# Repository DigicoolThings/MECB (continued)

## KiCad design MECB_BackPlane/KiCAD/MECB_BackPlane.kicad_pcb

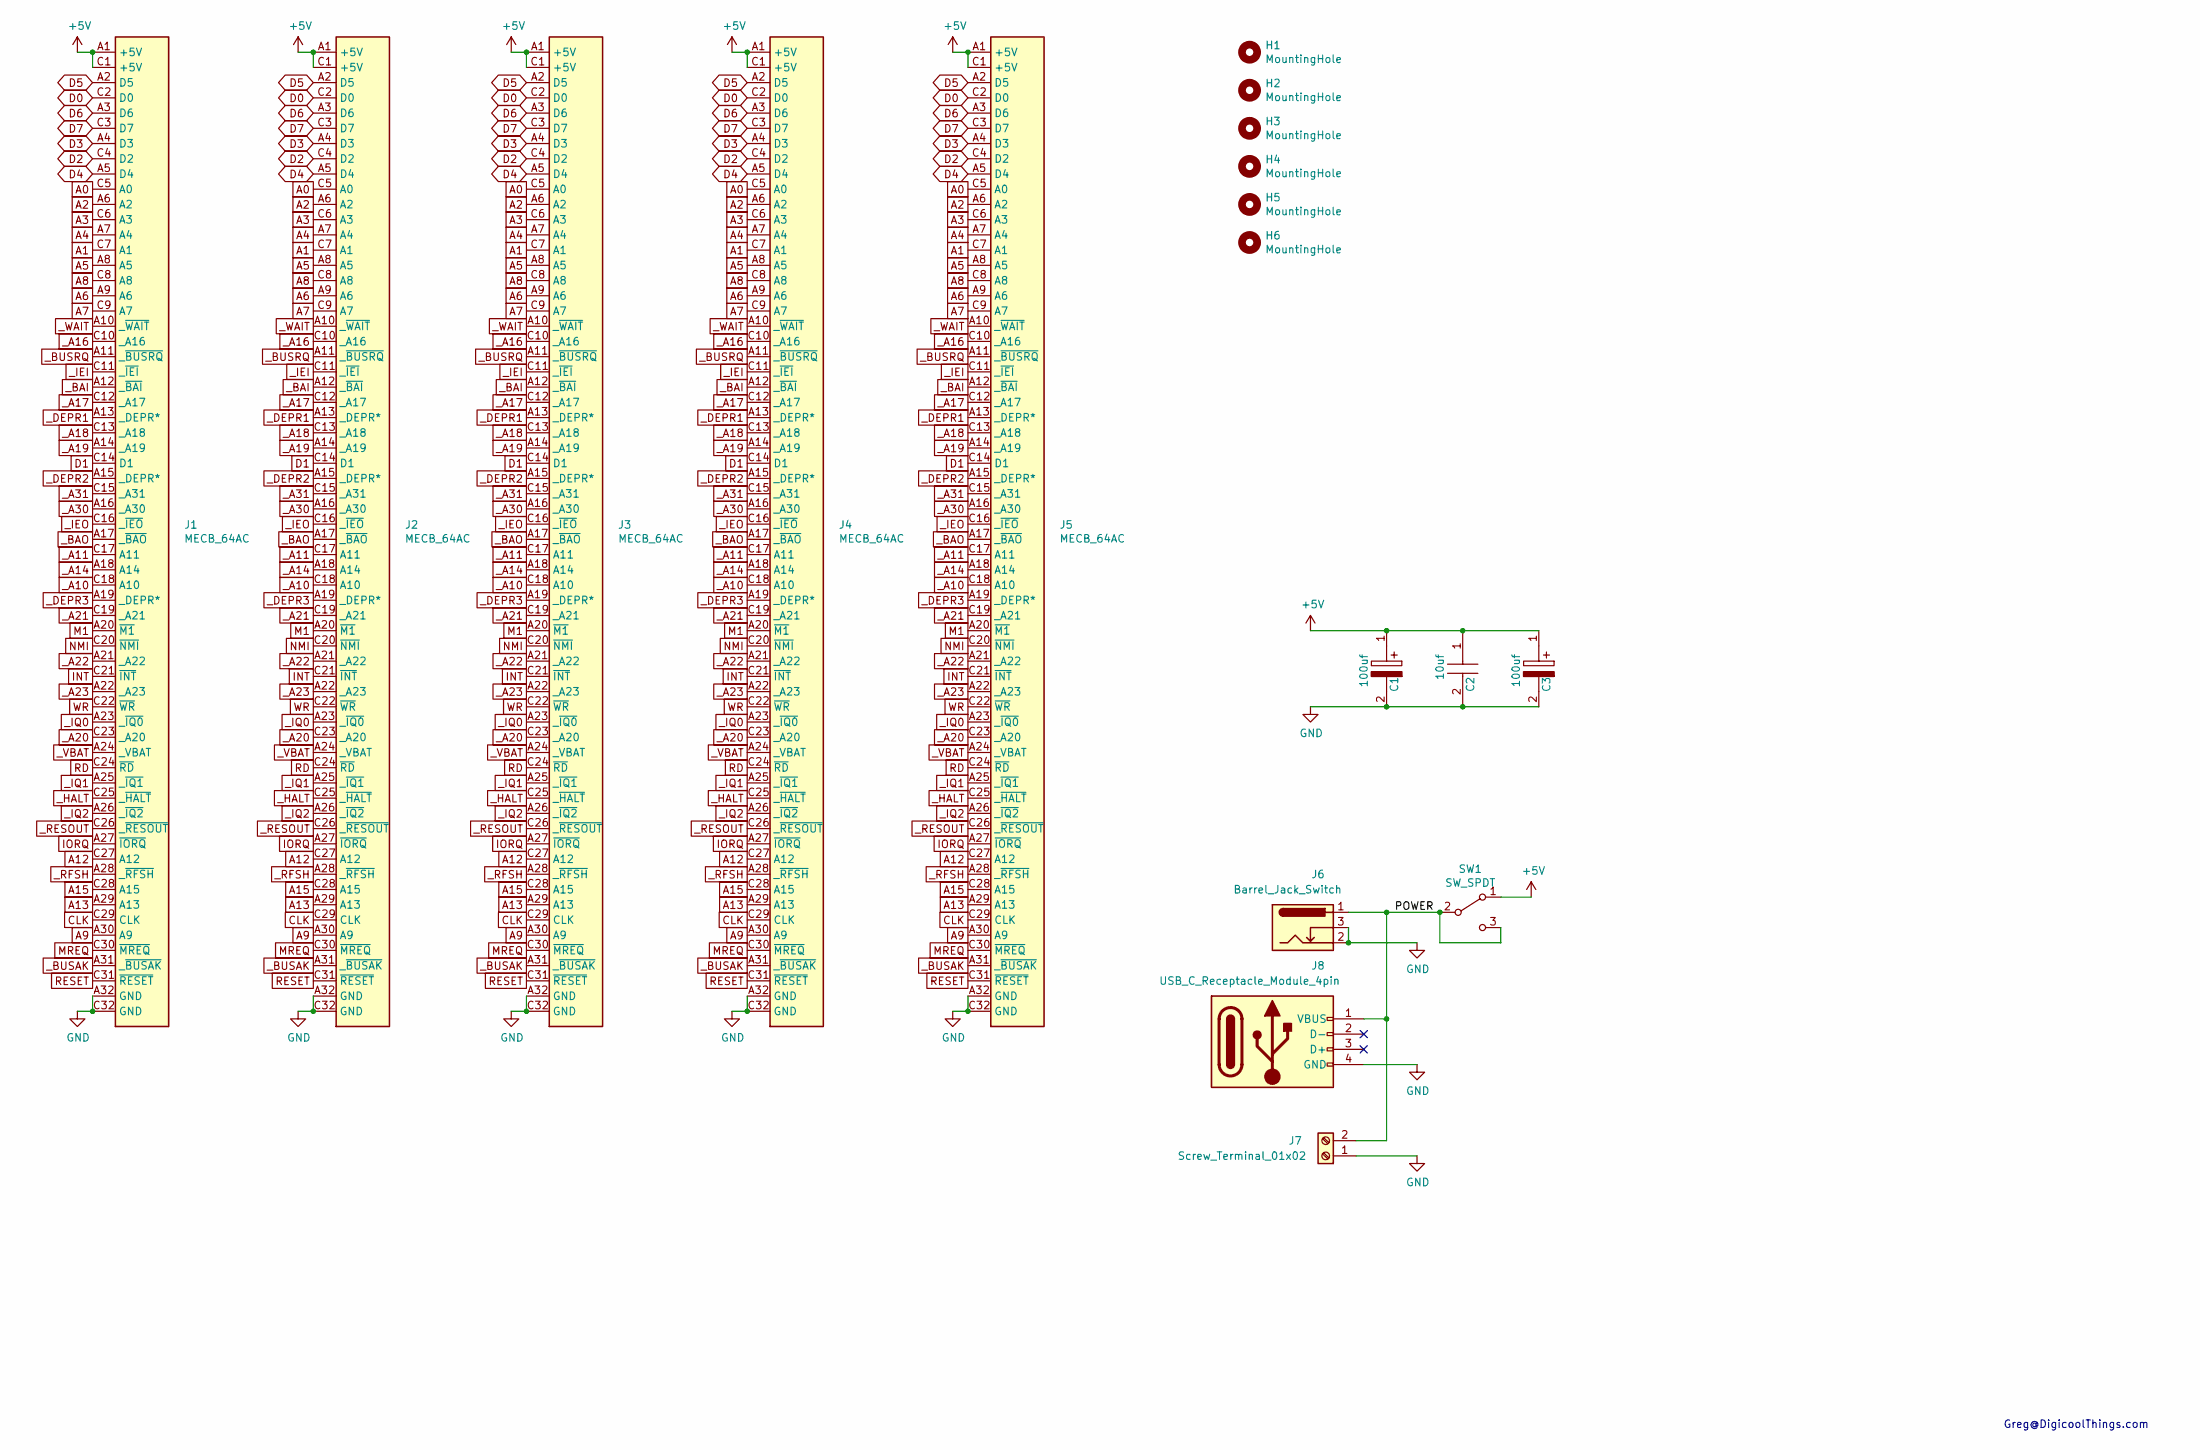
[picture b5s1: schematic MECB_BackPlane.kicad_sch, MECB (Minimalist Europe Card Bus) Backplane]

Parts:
C1, C3: 100uf; CAPPRD250W50D630H800-5mm
C2: 10uf; FG24
H1, H2, H3, H4, H5, H6: MountingHole; MountingHole_3.2mm_M3
J1, J2, J3, J4: MECB_64AC; DIN41612_C_2x32_C64AC_Female_Vertical_THT
J5: MECB_64AC; DIN41612_C_2x32_C64AC_Female_Horizontal_THT
J6: Barrel_Jack_Switch; BarrelJack_Horizontal
J7: Screw_Terminal_01x02; TerminalBlock_Philmore_TB132_1x02_P5.00mm_Horizontal
J8: USB_C_Receptacle_Module_4pin; USB_Module_4pin_Header_P2.54mm
SW1: SW_SPDT; Switch-SPST-4.7-lug

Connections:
+5V: C1.1, C2.1, C3.1, J1.A1 (+5V), J1.C1 (+5V), J2.A1 (+5V), J2.C1 (+5V), J3.A1 (+5V), J3.C1 (+5V), J4.A1 (+5V), J4.C1 (+5V), J5.A1 (+5V), J5.C1 (+5V), SW1.1 (A)
/POWER: J6.1, J7.2, J8.1 (VBUS), SW1.2 (B), SW1.3 (C)
A0: J1.C5 (A0), J2.C5 (A0), J3.C5 (A0), J4.C5 (A0), J5.C5 (A0)
A1: J1.C7 (A1), J2.C7 (A1), J3.C7 (A1), J4.C7 (A1), J5.C7 (A1)
A2: J1.A6 (A2), J2.A6 (A2), J3.A6 (A2), J4.A6 (A2), J5.A6 (A2)
A3: J1.C6 (A3), J2.C6 (A3), J3.C6 (A3), J4.C6 (A3), J5.C6 (A3)
A4: J1.A7 (A4), J2.A7 (A4), J3.A7 (A4), J4.A7 (A4), J5.A7 (A4)
A5: J1.A8 (A5), J2.A8 (A5), J3.A8 (A5), J4.A8 (A5), J5.A8 (A5)
A6: J1.A9 (A6), J2.A9 (A6), J3.A9 (A6), J4.A9 (A6), J5.A9 (A6)
A7: J1.C9 (A7), J2.C9 (A7), J3.C9 (A7), J4.C9 (A7), J5.C9 (A7)
A8: J1.C8 (A8), J2.C8 (A8), J3.C8 (A8), J4.C8 (A8), J5.C8 (A8)
A9: J1.A30 (A9), J2.A30 (A9), J3.A30 (A9), J4.A30 (A9), J5.A30 (A9)
A12: J1.C27 (A12), J2.C27 (A12), J3.C27 (A12), J4.C27 (A12), J5.C27 (A12)
A13: J1.A29 (A13), J2.A29 (A13), J3.A29 (A13), J4.A29 (A13), J5.A29 (A13)
A15: J1.C28 (A15), J2.C28 (A15), J3.C28 (A15), J4.C28 (A15), J5.C28 (A15)
CLK: J1.C29 (CLK), J2.C29 (CLK), J3.C29 (CLK), J4.C29 (CLK), J5.C29 (CLK)
D0: J1.C2 (D0), J2.C2 (D0), J3.C2 (D0), J4.C2 (D0), J5.C2 (D0)
D1: J1.C14 (D1), J2.C14 (D1), J3.C14 (D1), J4.C14 (D1), J5.C14 (D1)
D2: J1.C4 (D2), J2.C4 (D2), J3.C4 (D2), J4.C4 (D2), J5.C4 (D2)
D3: J1.A4 (D3), J2.A4 (D3), J3.A4 (D3), J4.A4 (D3), J5.A4 (D3)
D4: J1.A5 (D4), J2.A5 (D4), J3.A5 (D4), J4.A5 (D4), J5.A5 (D4)
D5: J1.A2 (D5), J2.A2 (D5), J3.A2 (D5), J4.A2 (D5), J5.A2 (D5)
D6: J1.A3 (D6), J2.A3 (D6), J3.A3 (D6), J4.A3 (D6), J5.A3 (D6)
D7: J1.C3 (D7), J2.C3 (D7), J3.C3 (D7), J4.C3 (D7), J5.C3 (D7)
GND: C1.2, C2.2, C3.2, J1.A32 (GND), J1.C32 (GND), J2.A32 (GND), J2.C32 (GND), J3.A32 (GND), J3.C32 (GND), J4.A32 (GND), J4.C32 (GND), J5.A32 (GND), J5.C32 (GND), J6.2, J6.3, J7.1, J8.4 (GND)
INT: J1.C21 (~INT), J2.C21 (~INT), J3.C21 (~INT), J4.C21 (~INT), J5.C21 (~INT)
IORQ: J1.A27 (~IORQ), J2.A27 (~IORQ), J3.A27 (~IORQ), J4.A27 (~IORQ), J5.A27 (~IORQ)
M1: J1.A20 (~M1), J2.A20 (~M1), J3.A20 (~M1), J4.A20 (~M1), J5.A20 (~M1)
MREQ: J1.C30 (~MREQ), J2.C30 (~MREQ), J3.C30 (~MREQ), J4.C30 (~MREQ), J5.C30 (~MREQ)
NMI: J1.C20 (~NMI), J2.C20 (~NMI), J3.C20 (~NMI), J4.C20 (~NMI), J5.C20 (~NMI)
RD: J1.C24 (~RD), J2.C24 (~RD), J3.C24 (~RD), J4.C24 (~RD), J5.C24 (~RD)
RESET: J1.C31 (~RESET), J2.C31 (~RESET), J3.C31 (~RESET), J4.C31 (~RESET), J5.C31 (~RESET)
WR: J1.C22 (~WR), J2.C22 (~WR), J3.C22 (~WR), J4.C22 (~WR), J5.C22 (~WR)
_A10: J1.C18 (A10), J2.C18 (A10), J3.C18 (A10), J4.C18 (A10), J5.C18 (A10)
_A11: J1.C17 (A11), J2.C17 (A11), J3.C17 (A11), J4.C17 (A11), J5.C17 (A11)
_A14: J1.A18 (A14), J2.A18 (A14), J3.A18 (A14), J4.A18 (A14), J5.A18 (A14)
_A16: J1.C10 (_A16), J2.C10 (_A16), J3.C10 (_A16), J4.C10 (_A16), J5.C10 (_A16)
_A17: J1.C12 (_A17), J2.C12 (_A17), J3.C12 (_A17), J4.C12 (_A17), J5.C12 (_A17)
_A18: J1.C13 (_A18), J2.C13 (_A18), J3.C13 (_A18), J4.C13 (_A18), J5.C13 (_A18)
_A19: J1.A14 (_A19), J2.A14 (_A19), J3.A14 (_A19), J4.A14 (_A19), J5.A14 (_A19)
_A20: J1.C23 (_A20), J2.C23 (_A20), J3.C23 (_A20), J4.C23 (_A20), J5.C23 (_A20)
_A21: J1.C19 (_A21), J2.C19 (_A21), J3.C19 (_A21), J4.C19 (_A21), J5.C19 (_A21)
_A22: J1.A21 (_A22), J2.A21 (_A22), J3.A21 (_A22), J4.A21 (_A22), J5.A21 (_A22)
_A23: J1.A22 (_A23), J2.A22 (_A23), J3.A22 (_A23), J4.A22 (_A23), J5.A22 (_A23)
_A30: J1.A16 (_A30), J2.A16 (_A30), J3.A16 (_A30), J4.A16 (_A30), J5.A16 (_A30)
_A31: J1.C15 (_A31), J2.C15 (_A31), J3.C15 (_A31), J4.C15 (_A31), J5.C15 (_A31)
_BAI: J1.A12 (_~BAI), J2.A12 (_~BAI), J3.A12 (_~BAI), J4.A12 (_~BAI), J5.A12 (_~BAI)
_BAO: J1.A17 (_~BAO), J2.A17 (_~BAO), J3.A17 (_~BAO), J4.A17 (_~BAO), J5.A17 (_~BAO)
_BUSAK: J1.A31 (_~BUSAK), J2.A31 (_~BUSAK), J3.A31 (_~BUSAK), J4.A31 (_~BUSAK), J5.A31 (_~BUSAK)
_BUSRQ: J1.A11 (_~BUSRQ), J2.A11 (_~BUSRQ), J3.A11 (_~BUSRQ), J4.A11 (_~BUSRQ), J5.A11 (_~BUSRQ)
_DEPR1: J1.A13 (_DEPR*), J2.A13 (_DEPR*), J3.A13 (_DEPR*), J4.A13 (_DEPR*), J5.A13 (_DEPR*)
_DEPR2: J1.A15 (_DEPR*), J2.A15 (_DEPR*), J3.A15 (_DEPR*), J4.A15 (_DEPR*), J5.A15 (_DEPR*)
_DEPR3: J1.A19 (_DEPR*), J2.A19 (_DEPR*), J3.A19 (_DEPR*), J4.A19 (_DEPR*), J5.A19 (_DEPR*)
_HALT: J1.C25 (_~HALT), J2.C25 (_~HALT), J3.C25 (_~HALT), J4.C25 (_~HALT), J5.C25 (_~HALT)
_IEI: J1.C11 (_~IEI), J2.C11 (_~IEI), J3.C11 (_~IEI), J4.C11 (_~IEI), J5.C11 (_~IEI)
_IEO: J1.C16 (_~IEO), J2.C16 (_~IEO), J3.C16 (_~IEO), J4.C16 (_~IEO), J5.C16 (_~IEO)
_IQ0: J1.A23 (_~IQ0), J2.A23 (_~IQ0), J3.A23 (_~IQ0), J4.A23 (_~IQ0), J5.A23 (_~IQ0)
_IQ1: J1.A25 (_~IQ1), J2.A25 (_~IQ1), J3.A25 (_~IQ1), J4.A25 (_~IQ1), J5.A25 (_~IQ1)
_IQ2: J1.A26 (_~IQ2), J2.A26 (_~IQ2), J3.A26 (_~IQ2), J4.A26 (_~IQ2), J5.A26 (_~IQ2)
_RESOUT: J1.C26 (_~RESOUT), J2.C26 (_~RESOUT), J3.C26 (_~RESOUT), J4.C26 (_~RESOUT), J5.C26 (_~RESOUT)
_RFSH: J1.A28 (_~RFSH), J2.A28 (_~RFSH), J3.A28 (_~RFSH), J4.A28 (_~RFSH), J5.A28 (_~RFSH)
_VBAT: J1.A24 (_VBAT), J2.A24 (_VBAT), J3.A24 (_VBAT), J4.A24 (_VBAT), J5.A24 (_VBAT)
_WAIT: J1.A10 (_~WAIT), J2.A10 (_~WAIT), J3.A10 (_~WAIT), J4.A10 (_~WAIT), J5.A10 (_~WAIT)

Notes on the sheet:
Greg@DigicoolThings.com

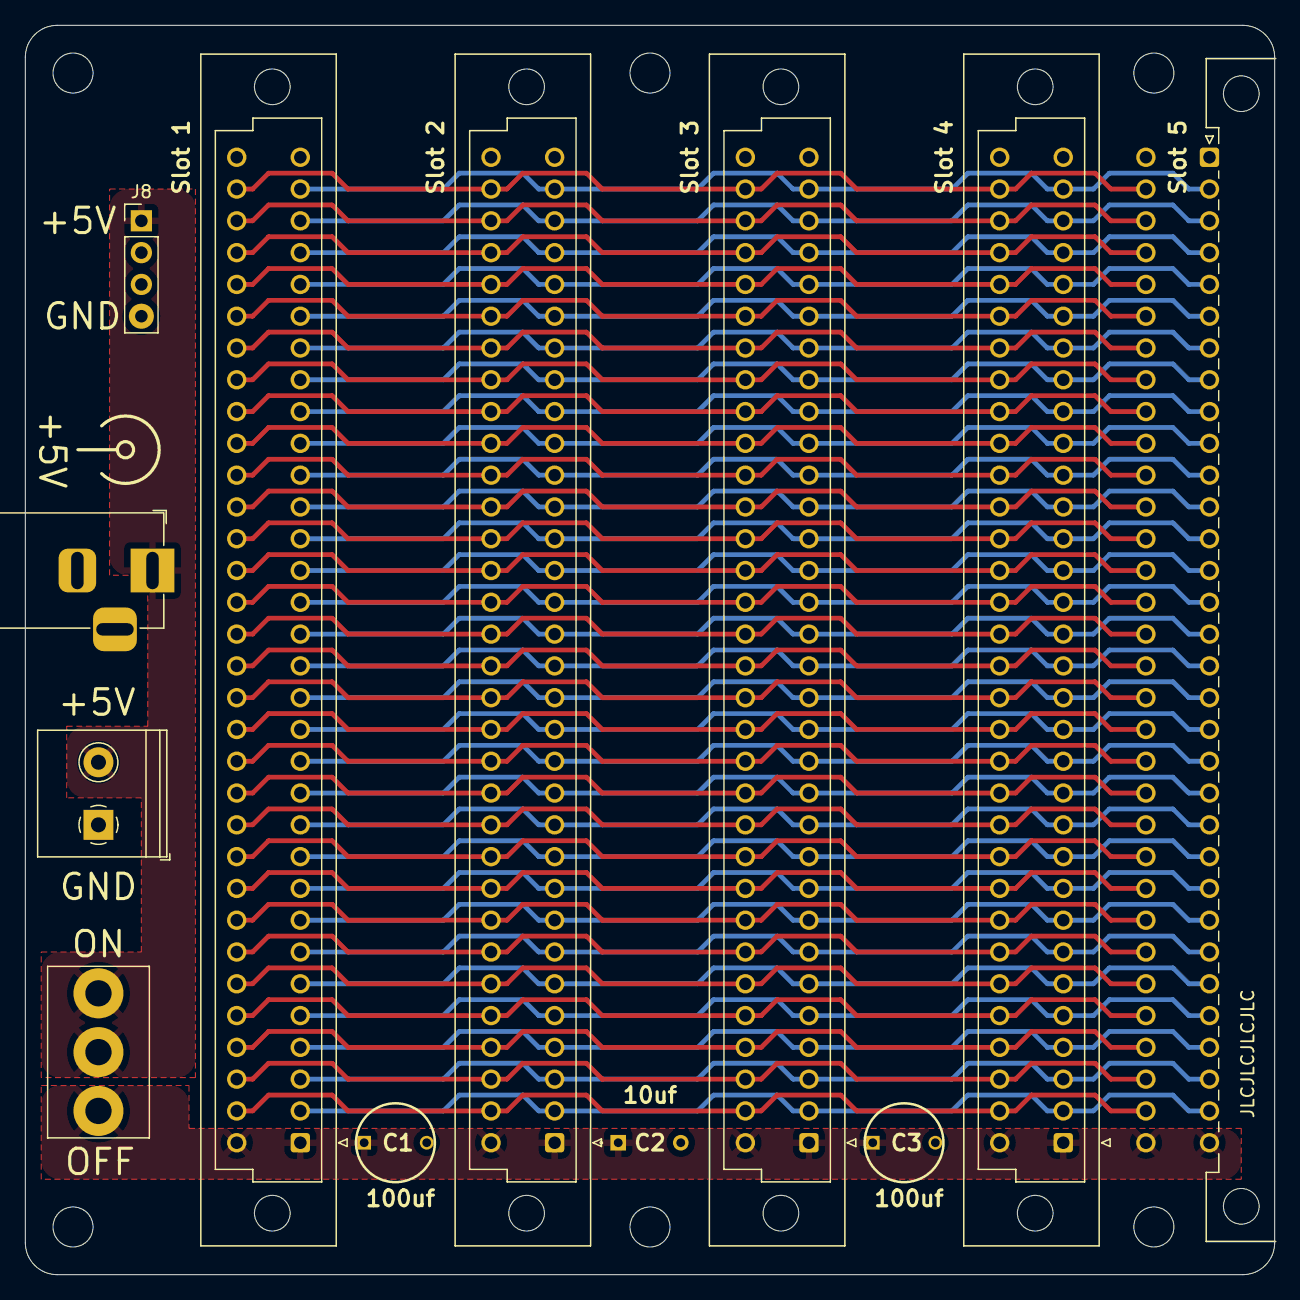
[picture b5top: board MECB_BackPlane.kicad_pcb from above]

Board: 2 copper layers, 99.8 x 99.8 mm, 18 parts (0 on the bottom side), 63 nets.

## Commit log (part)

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2022-03-01 Update README.md
    Initial README,md TL;DR
2022-03-01 Update README.md
    Add MECB Board Mechanical image.
2022-03-02 Initial commit of KiCAD v6 MECB_Template folder, Board Mechanical Specification PDF, and associated README updates.
2023-01-15 Initial commit of 6809 CPU card & TMS992xA VDP card WinCupl PAL source and 6809 initial test assembly source
2023-01-15 Correct small typo in setVramBlock subroutine function comments.
2023-01-16 Redefined to now assign active low signals at the pin declaration, so all logic definitions are now consistently positive logic assertions (therefore easier to read and avoid inverse logic errors).
2023-07-17 Update MECB_Template files to KiCAD v7
2023-07-17 Update README.md for KiCAD v7 reference.
2023-07-17 Add KiCAD Gerbers and Project files for currently completed MECB Cards. i.e. MECB_Backplane, MECB_Prototype, and MECB_TMS992xA_VDP Cards.
2023-07-17 Normalise folder card structure and inclusion of Gerbers and PDF viewable Schematics.
2023-07-20 Add Assembled board images. Add correct schematic for MECB_BackPlane.
2023-10-01 Add assembly source for the RAM version of InitialTest09, and the three Christmas09 VDP and Sound test demos.
2023-10-11 Add NOP (commented out) - required when running at 4Mhz
2023-10-28 Various board resource additions,6809 source and ROM images.
2023-11-12 Add 6809 CPU Card BOM PDF
2024-01-23 Add MECB Bus Pinout v1.0
2024-01-23 Update README.md
    Add MECB Bus Pinout image.
2024-03-22 Add MECB 1MB ROM Expansion Card folder and gerbers etc. Update 6809 CPU Card PLD Source for additional Memory Map options. Add ASSIST09 original Source Code made compatible with ASM6809 Assembler. Ad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
2024-03-27 Add SST38SF040 ROM binary image for ROM Expansion Card (ASSIST09 + BASIC09), with $C0 I/O page.
2024-04-12 Changes for MECB 6809 CPU Card v2.3 update
2024-05-03 Add v2.0 MECB TMS VDP Card, which adds TMS9918 support to existing TMS992x Card (hence renamed folder)
2024-05-03 Remove obsoleted pre-v2.0 MECB TMS992xA VDP folder.
2024-05-11 Minor update to v2.4. Due to an oversight, v2.3 inadvertantly included a double-up ROM_WR pull-up resistor. This doesn't cause any isues, so v2.4 is just a tidy-up, which also allowed returning to se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
2024-06-07 Add MECB_6502_CPU_Card. Also a small correction to 6809 CPU Card BOM (remove surplus 74HCT244 line).
2024-06-15 Added HD63C09_PLCC-DIP40_Adapter Gerbers and Schematic PDF to MECB_6809_CPU project
2024-07-12 Correct missing '#' (typo) in HelloWorld.6502.asm, as noted by Michael. No functional difference, as the error was in initialising the Stack Pointer (and we aren't using the Stack in this simple prog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
2024-07-13 Update KiCAD Template files for KiCAD v8 (no functional change).
2024-07-13 Update MECB_6502_CPU for v1.2 - Minor version change for update of PLD (U1) & ROM (U4) footprints to be ZIF socket friendly (1.0mm pad holes, instead of 0.8mm).
2024-07-14 Update MECB_6809_CPU to v2.5 - Minor version change for update of PLD (U1) & ROM (U4) footprints to be ZIF socket friendly (1.0mm pad holes, instead of 0.8mm).
2024-07-21 Update WinCUPL source files for 6502_CPU / Motorola_IO / TMS992x_VDP for CreatiVision re-Creation (commented out).
2024-07-27 Add new MECB_Prototype_PLD resources.
2024-08-15 Add resources for MECB_6309_CPU_PLCC (v1.1)
2024-08-15 Add MECB_Pinout_Handout tp MECB_Prototype (Same as MECB_Prototype_PLD)
2024-08-25 Various MECB project resource updates.
2024-08-29 Minor MECB_6502_CPU update to silkscreens (non-functional changes). Updated BOM for v1.3. Added v1.3 Assembled board photo.
2024-10-26 Add MECB_Backplane_Extension v1.0 - PLEASE NOTE: This is currently untested. Use gerbers at your own risk!
2024-11-13 Commiting latest versions of WinCupl source.
2024-11-13 Corrections and clean-up of WinCupl source, mostly of CreatiVision memory map definitions (to utilise clk instead of mreq).
2024-11-15 Added CreatiVision ROM0 + ROM1 images for MECB_1MB_ROM_Expansion. Added PLD compiled .jed files to all WinCupl folders, to allow easy PLD Programming without need for WinCupl install.
2024-11-15 Added CreatiVision DiagnosticB ROM image to MECB_6502_CPU project (AT28C256_CreatiVision_DiagnosticB.bin), to allow CreatiVision re-Creation testing without a 1MB ROM Expansion Card.
2025-02-20 MECB_Motorola_IO v1.2 update - Trivial update to change Audio Out header from 2-pin to 3-pin, for consistency with other new MECB Cards with Audio Out headers. Also adding Schematic PDFs and PCB rend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
2025-04-17 Add specific source and binary images for ASSIST09 48K/16K and 56K/8K memory maps.
2025-04-17 Updated MECB_6809_CPU assembled photos clarifying 56K/8K and 48K/16K memory maps and DIP switch settings.
2025-05-04 Add new KiCAD Template for 22V10 PLD, and update prior 16V8 PLD template for KiCAD v9.0.1. The two new named templates, replace the prior sinfle template (16V8 based).
2025-05-04 Update README.md for new KiCAD Templates
2025-05-08 Add Programmers Guide and 6809 Assembly TEXT mode test source code, to MECB_TMS9918_or_TMS992x_VDP
2025-05-08 Add MECB_V9938_or_V9958_VDP project resources.
2025-05-08 Fixing a naming case-sensitive issue.
2025-05-08 Renaming of WinCUPL files to clarify 16V8 vs 22V10 device selection.
2025-05-08 Renaming of WinCUPL files to clarify 16V8 vs 22V10 device selection (naming case consistancy adjustments).
2025-05-14 Rename / Update MECB_Prototype_16V8
2025-05-30 Add MECB_Prototype_22V10 folder and resources. Add MECB_Prototype_16V8 BOM. Rename .jed file (for naming consistancy).
2025-06-27 Add MECB_WDC_W65C02S_PLCC_CPU. Also, updates to MECB_Prototype_22V10 WinCupl files.
2025-08-02 Add new MECB_Grid + MECB_Grid_16V8 + MECB_Grid_22V10 Card folders and resources.
2025-08-22 Add MECB_OLED_Display_128x64 folder and resources.
2025-11-14 Add CHIPOS ROM images to MECB_6809_CPU and MECB_6309_CPU_PLCC folders. Note: These ROM images require additional system boards as per the DREAM 6800 (6809) re-Creation project.
2025-11-16 Correct CHIPOS oversight in my 6809 conversion related to STORV routine and difference between 6800 & 6809 Stack Pointer handling. A big thanks to David (djrm on Forum), for detecting and reporting t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
2026-01-16 Added BOM (.pdf & .png) for MECB_Motorola_IO
2026-01-16 MECB_Motorola_IO - Minor update to Gerbers (silkscreen only). Updated PCB 3D Renders. Rename Schematic (current / no version number).
2026-01-17 MECB_Motorola_IO - Minor clarification on BOM item description.
2026-02-08 Initial commit of MECB_68008_CPU & MECB_6802_CPU resources.
2026-02-14 MECB_6802_CPU - Correct the WinCUPL source and compiled .jed files, to resolve logic error reported by Emil.
2026-02-17 MECB_68008_CPU - Update BOM
2026-02-25 MECB_68008_CPU - Add Xmas_OLED demo / test. Add Motorola Educational Computer Board User Manual (MecbManual.pdf).
2026-04-06 Update MECB KiCAD Templates. Include 220nf bypass capacitor. Re-route tracks based on new capacitor positioning. Update 3D images to be new blue colouring. Correct earth zone inner corner rounding.
2026-04-13 MECB_6802_CPU v1.0 minor updates and corrections.
2026-04-19 MECB_OLED_Display_128x64 - Added OLED_128x64_Test.S19 and OLED_128x64_Test.lst files, to enable quick testing without needing to first assemble the .asm source code file.
2026-04-23 MECB_6802_CPU - Corrections to WinCUPL code and compiled .jed files.
2026-05-22 MECB_6802_CPU v1.0 - Update / add all resource files for YouTube video.
